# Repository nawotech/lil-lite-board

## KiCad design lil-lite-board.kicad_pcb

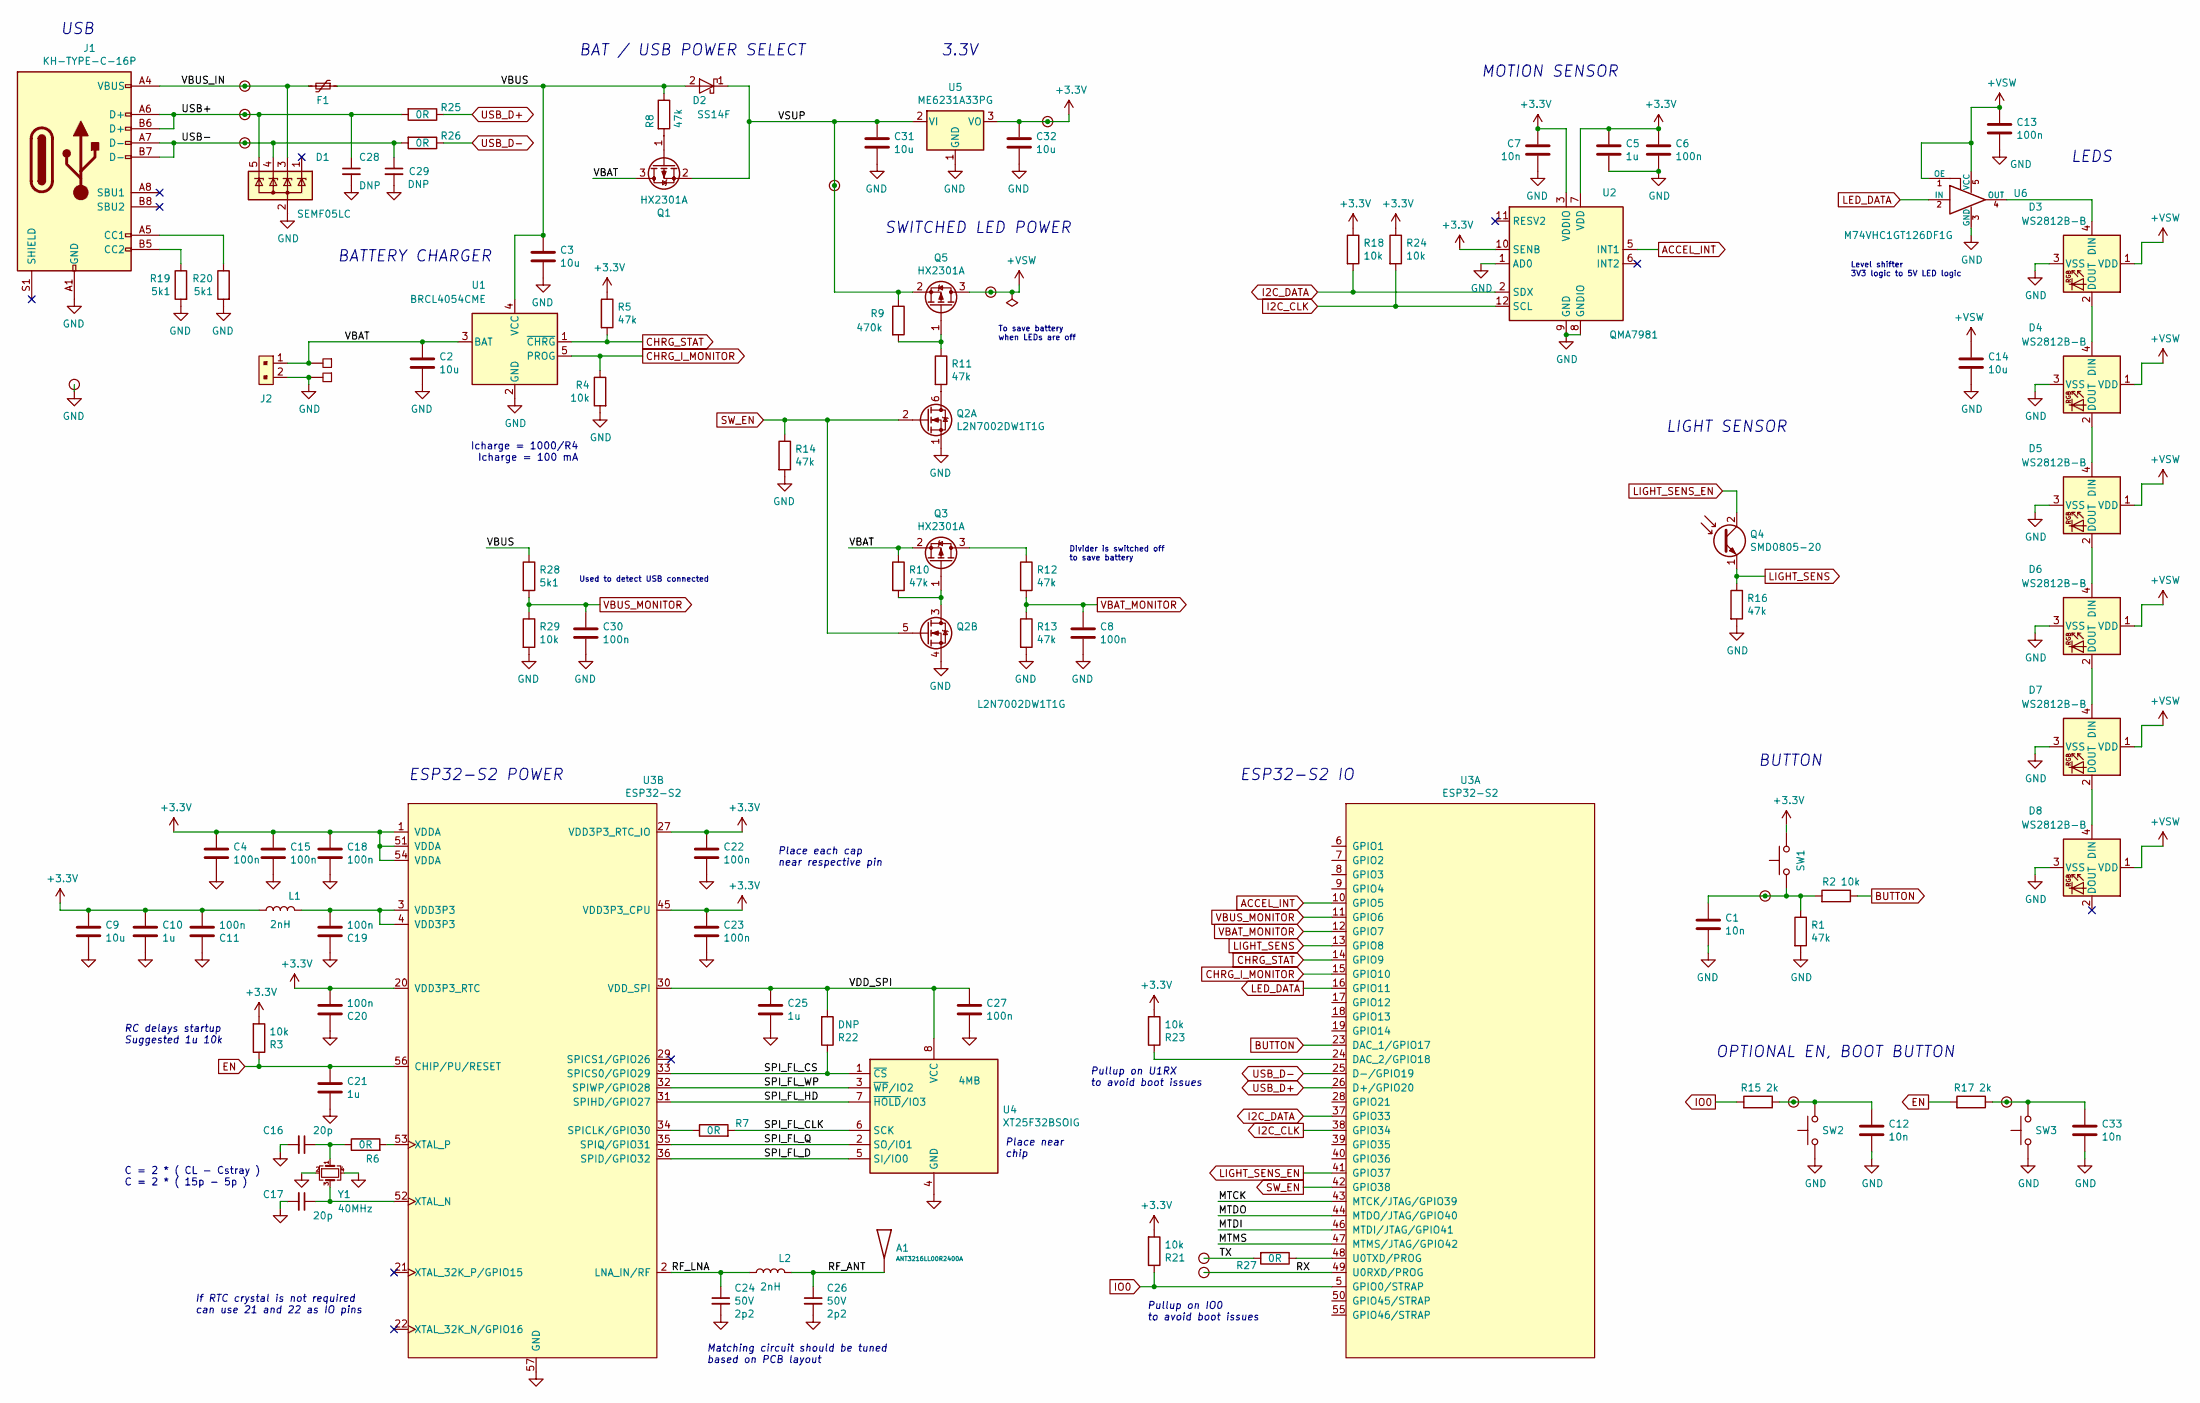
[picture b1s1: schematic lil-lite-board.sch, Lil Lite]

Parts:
A1: ANT3216LL00R2400A; Antenna_3216
C1, C7, C12, C33: 10n; C_0603_1608Metric; Voltage 100; LCSC Part Number C77439
C2, C3, C9, C14, C31, C32: 10u; C_0603_1608Metric; LCSC Part Number C319196
C4, C6, C8, C11, C13, C15, C18, C19, C20, C22, C23, C27, C30: 100n; C_0402_1005Metric; LCSC Part Number C60474
C5, C10, C21, C25: 1u; C_0402_1005Metric; LCSC Part Number C497333
C16, C17: C_0402_50V_COG_20p; C_0402_1005Metric; Voltage 50V
C24, C26: C_0402_50V_COG_2p2; C_0402_1005Metric; Voltage 50V
C28, C29: DNP; C_0402_1005Metric; Voltage 50V
D1: SEMF05LC; SOT-353_SC-70-5; LCSC Part Number C355236
D2: SS14F; D_SMA; LCSC Part Number C108832
D3, D4, D5, D6, D7, D8: WS2812B-B; LED_WS2812B_PLCC4_5.0x5.0mm_P3.2mm; LCSC Part Number C114586
F1: MF-FSMF050X-2; Fuse_0603_1608Metric; LCSC Part Number C210357
J1: KH-TYPE-C-16P; USB_C_Receptacle_KH-TYPE-C-16P
J2: S2B-PH-SM4-TB; PinHeader_2x1mm_P2mm_SMD_RA; MPN S2B-PH-SM4-TB(LF)(SN); Digi-Key_PN 455-1749-1-ND
L1, L2: HQ1005C2N0ST; L_0402_1005Metric
P2, P3: WirePad; Solder_Wire_Pad_5mmx3mm
Q1, Q3, Q5: HX2301A; SOT-23
Q2: L2N7002DW1T1G; SOT-363_SC-70-6
Q4: SMD0805-20; LED_0805_2012Metric; LCSC Part Number C250858
R1, R5, R8, R10, R11, R12, R13, R16: 47k; R_0402_1005Metric; LCSC Part Number C380741
R2, R3, R4, R18, R21, R23, R24: 10k; R_0402_1005Metric; LCSC Part Number C60490
R6, R7, R25, R26, R27: 0R; R_0402_1005Metric
R9: 470k; R_0402_1005Metric; LCSC Part Number C409715
R14: 47k; R_0402_1005Metric; Tolerance 1%
R15, R17: 2k; R_0402_1005Metric; LCSC Part Number C60490
R19, R20, R28: 5k1; R_0402_1005Metric
R22: DNP; R_0402_1005Metric
R29: 10k; R_0402_1005Metric
SW1: TS5220A; SW_SPST_TL3342
SW2, SW3: DNP; STO-060A16AB
TP5, TP6, TP7, TP8, TP9, TP10, TP11, TP12, TP14, TP17, TP18, TP19: TestPoint_ICT_1mm; ICT_TestPoint_Pad_D1.00mm
U1: BRCL4054CME; SOT-23-5; LCSC Part Number C305436
U2: QMA7981; LGA-12_2x2mm_P0.5mm
U3: ESP32-S2
U4: XT25F32BSOIG; SOIC-8_3.9x4.9mm_P1.27mm
U5: ME6231A33PG; SOT-89-3
U6: M74VHC1GT126DF1G; SOT-353_SC-70-5
Y1: X322540MPB4SI; Crystal_SMD_3225-4Pin_3.2x2.5mm

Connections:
+3V3: C4.1, C5.1, C6.1, C7.1, C9.1, C10.1, C11.2, C15.1, C18.1, C20.2, C22.1, C23.1, C32.1, L1.1, R3.2, R5.1, R18.1, R21.2, R23.2, R24.1, SW1.1, TP19.1, U2.3 (VDDIO), U2.7 (VDD), U2.10 (SENB), U3.1 (VDDA), U3.20 (VDD3P3_RTC), U3.27 (VDD3P3_RTC_IO), U3.45 (VDD3P3_CPU), U3.51 (VDDA), U3.54 (VDDA), U5.3 (VO)
+VSW: C13.1, C14.1, D3.1 (VDD), D4.1 (VDD), D5.1 (VDD), D6.1 (VDD), D7.1 (VDD), D8.1 (VDD), Q5.3 (D), TP18.1, U6.1 (OE), U6.5 (VCC)
/MTCK: U3.43 (MTCK/JTAG/GPIO39)
/MTDI: U3.46 (MTDI/JTAG/GPIO41)
/MTDO: U3.44 (MTDO/JTAG/GPIO40)
/MTMS: U3.47 (MTMS/JTAG/GPIO42)
/RF_ANT: A1.1, C26.1, L2.2
/RF_LNA: C24.1, L2.1, U3.2 (LNA_IN/RF)
/RX: TP11.1, U3.49 (U0RXD/PROG)
/SPI_FL_CLK: R7.2, U4.6 (SCK)
/SPI_FL_CS: R22.1, U3.33 (SPICS0/GPIO29), U4.1 (~CS)
/SPI_FL_D: U3.36 (SPID/GPIO32), U4.5 (SI/IO0)
/SPI_FL_HD: U3.31 (SPIHD/GPIO27), U4.7 (~HOLD~/IO3)
/SPI_FL_Q: U3.35 (SPIQ/GPIO31), U4.2 (SO/IO1)
/SPI_FL_WP: U3.32 (SPIWP/GPIO28), U4.3 (~WP~/IO2)
/TX: R27.2, TP10.1
/USB+: C28.1, D1.5 (K), J1.A6 (D+), J1.B6 (D+), R25.2, TP6.1
/USB-: C29.1, D1.4 (K), J1.A7 (D-), J1.B7 (D-), R26.2, TP7.1
/VBAT: C2.1, J2.1, P2.1, Q1.3 (D), Q3.2 (S), R10.1, U1.3 (BAT)
/VBUS: C3.1, D2.2 (A), F1.1, R8.1, R28.1, U1.4 (VCC)
/VBUS_IN: D1.3 (K), F1.2, J1.A4 (VBUS), J1.A9 (VBUS), J1.B4 (VBUS), J1.B9 (VBUS), TP9.1
/VDD_SPI: C25.1, C27.1, R22.2, U3.30 (VDD_SPI), U4.8 (VCC)
/VSUP: C31.1, D2.1 (K), Q1.2 (S), Q5.2 (S), R9.1, TP17.1, U5.2 (VI)
ACCEL_INT: U2.5 (INT1), U3.10 (GPIO5)
BUTTON: R2.1, U3.23 (DAC_1/GPIO17)
CHRG_I_MONITOR: R4.1, U1.5 (PROG), U3.15 (GPIO10)
CHRG_STAT: R5.2, U1.1 (~CHRG), U3.14 (GPIO9)
EN: C21.1, R3.1, R17.2, U3.56 (CHIP/PU/RESET)
GND: C1.2, C2.2, C3.2, C4.2, C5.2, C6.2, C7.2, C8.2, C9.2, C10.2, C11.1, C12.2, C13.2, C14.2, C15.2, C16.2, C17.2, C18.2, C19.1, C20.1, C21.2, C22.2, C23.2, C24.2, C25.2, C26.2, C27.2, C28.2, C29.2, C30.2, C31.2, C32.2, C33.2, D1.2 (A), D3.3 (VSS), D4.3 (VSS), D5.3 (VSS), D6.3 (VSS), D7.3 (VSS), D8.3 (VSS), J1.A1 (GND), J1.A12 (GND), J1.B1 (GND), J1.B12 (GND), J2.2, P3.1, Q2.1 (S), Q2.4 (S), R1.2, R4.2, R13.2, R14.2, R16.2, R19.2, R20.2, R29.2, SW2.1, SW3.1, TP5.1, U1.2 (GND), U2.1 (AD0), U2.8 (GNDIO), U2.9 (GND), U3.57 (GND), U4.4 (GND), U5.1 (GND), U6.3 (GND), Y1.2, Y1.4
I2C_CLK: R24.2, U2.12 (SCL), U3.38 (GPIO34)
I2C_DATA: R18.2, U2.2 (SDX), U3.37 (GPIO33)
IO0: R15.2, R21.1, U3.5 (GPIO0/STRAP)
LED_DATA: U3.16 (GPIO11), U6.2 (IN)
LIGHT_SENS: Q4.1 (E), R16.1, U3.13 (GPIO8)
LIGHT_SENS_EN: Q4.2 (C), U3.41 (GPIO37)
unnamed: C1.1, R1.1, R2.2, SW1.2, TP8.1
unnamed: C12.1, R15.1, SW2.2, TP14.1
unnamed: C16.1, R6.1, Y1.1
unnamed: C17.1, U3.52 (XTAL_N), Y1.3
unnamed: C19.2, L1.2, U3.3 (VDD3P3), U3.4 (VDD3P3)
unnamed: C33.1, R17.1, SW3.2, TP12.1
unnamed: D3.2 (DOUT), D4.4 (DIN)
unnamed: D3.4 (DIN), U6.4 (OUT)
unnamed: D4.2 (DOUT), D5.4 (DIN)
unnamed: D5.2 (DOUT), D6.4 (DIN)
unnamed: D6.2 (DOUT), D7.4 (DIN)
unnamed: D7.2 (DOUT), D8.4 (DIN)
unnamed: J1.A5 (CC1), R20.1
unnamed: J1.B5 (CC2), R19.1
unnamed: Q1.1 (G), R8.2
unnamed: Q2.3 (D), Q3.1 (G), R10.2
unnamed: Q2.6 (D), R11.2
unnamed: Q3.3 (D), R12.1
unnamed: Q5.1 (G), R9.2, R11.1
unnamed: R6.2, U3.53 (XTAL_P)
unnamed: R7.1, U3.34 (SPICLK/GPIO30)
unnamed: R23.1, U3.24 (DAC_2/GPIO18)
unnamed: R27.1, U3.48 (U0TXD/PROG)
SW_EN: Q2.2 (G), Q2.5 (G), R14.1, U3.42 (GPIO38)
USB_D+: R25.1, U3.26 (D+/GPIO20)
USB_D-: R26.1, U3.25 (D-/GPIO19)
VBAT_MONITOR: C8.1, R12.2, R13.1, U3.12 (GPIO7)
VBUS_MONITOR: C30.1, R28.2, R29.1, U3.11 (GPIO6)

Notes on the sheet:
RC delays startup Suggested 1u 10k
C = 2 * ( CL - Cstray ) C = 2 * ( 15p - 5p )
If RTC crystal is not required can use 21 and 22 as IO pins
Pullup on U1RX to avoid boot issues
Place near chip
LEDS
Matching circuit should be tuned based on PCB layout
Icharge = 1000/R4 Icharge = 100 mA
MOTION SENSOR
LIGHT SENSOR
BUTTON
Level shifter 3V3 logic to 5V LED logic
3.3V
SWITCHED LED POWER
To save battery when LEDs are off
Divider is switched off to save battery
Used to detect USB connected
BATTERY CHARGER
USB
ESP32-S2 POWER
ESP32-S2 IO
BAT / USB POWER SELECT
Place each cap near respective pin
OPTIONAL EN, BOOT BUTTON
Pullup on IO0 to avoid boot issues

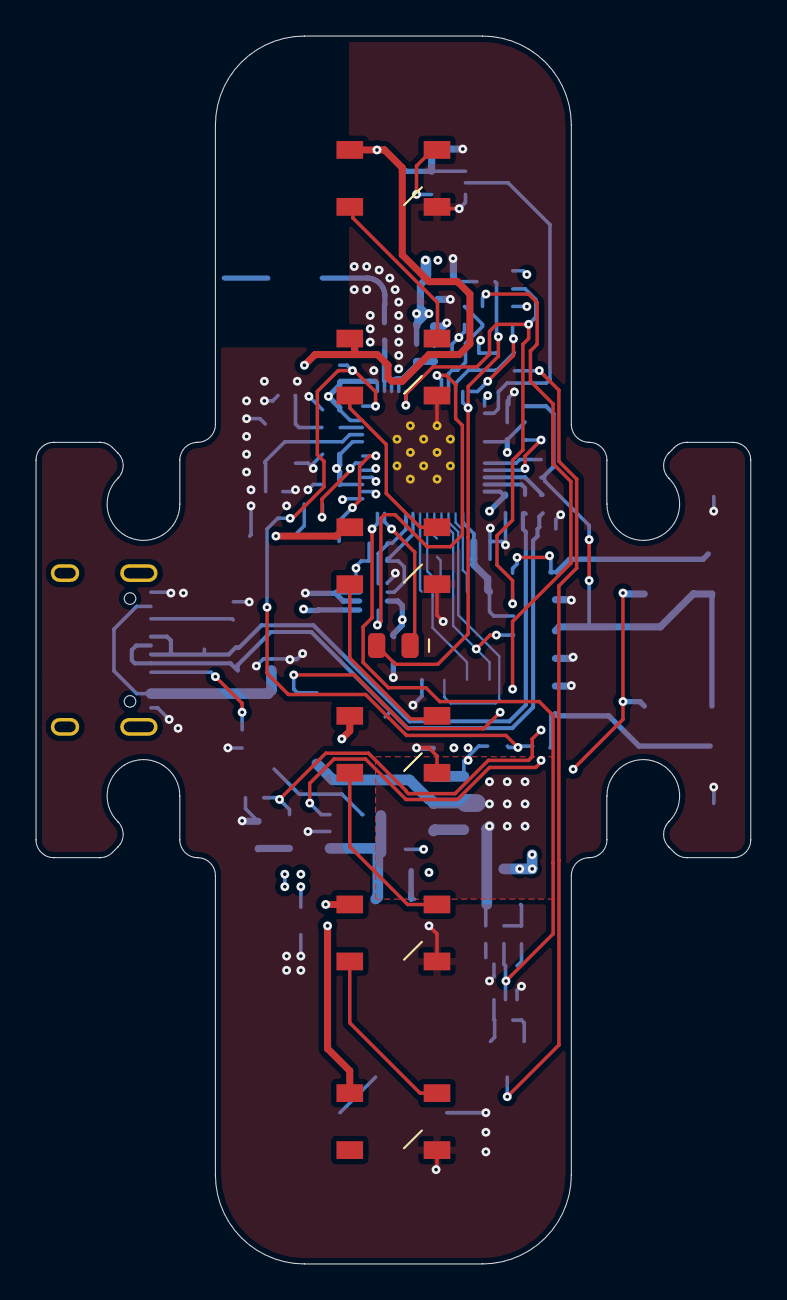
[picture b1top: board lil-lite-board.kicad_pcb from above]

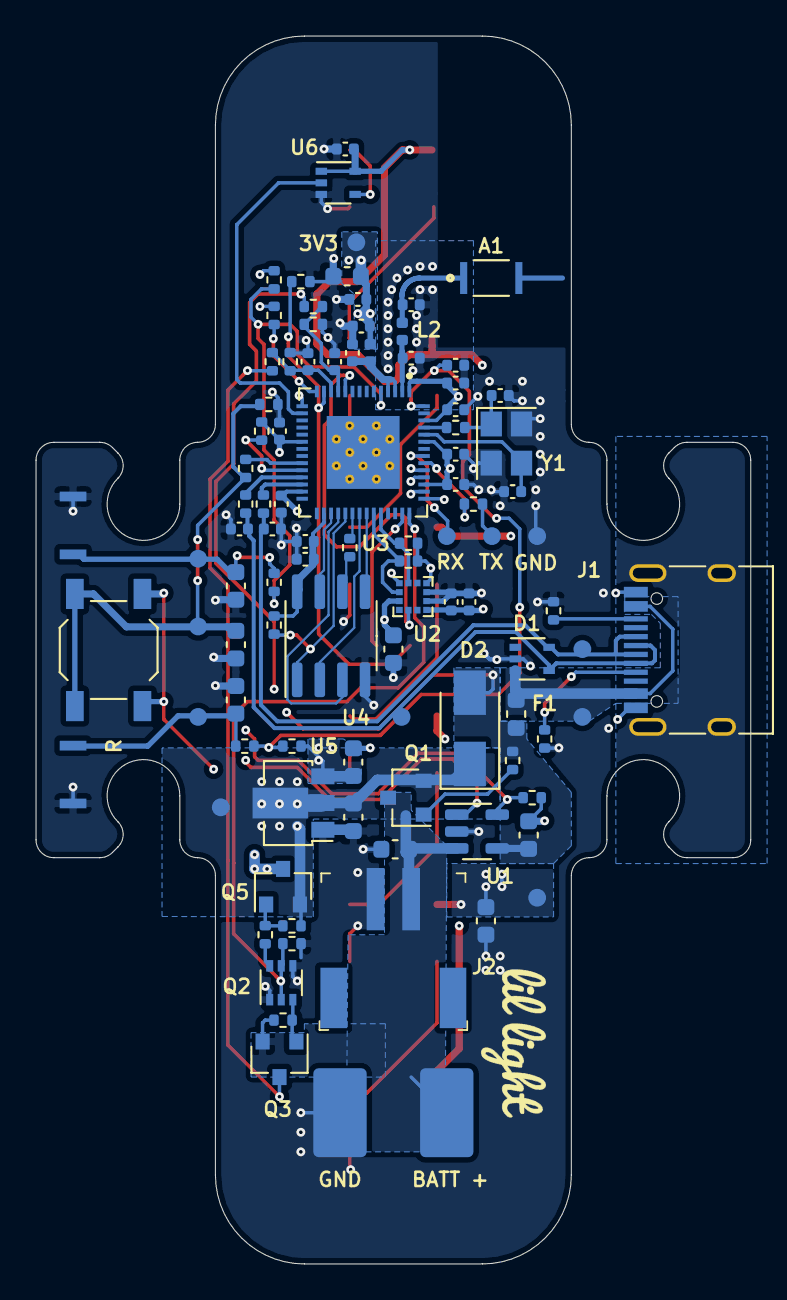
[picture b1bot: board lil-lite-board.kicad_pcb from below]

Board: 4 copper layers, 40.2 x 69.0 mm, 106 parts (99 on the bottom side), 59 nets.

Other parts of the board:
LG3: LOGO; Logo_Lil_Light_Long

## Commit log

2020-04-05 update gitignore
2020-04-05 update logo and BOM
2020-04-15 add schematic pdf
2020-05-06 update assemby drawing layer
2020-05-06 remove front led caps
2020-05-06 update 3d models
2020-05-06 remove old v1 files
2021-01-09 update broken library
2021-07-20 update board
2021-07-26 update to esp32-s2
2021-07-29 more updates
2021-08-01 clean up schematic
2021-08-05 placement
2021-08-07 routing done
2021-08-07 fix slkscreen
2021-08-07 Update BOM
2021-08-08 update schematic title block
2021-08-29 update flash chip to 4MB and divider for VBUS
2021-09-29 update flash chip to faster version
2021-10-05 add sw pn
2021-10-06 remove fab files
2021-10-14 update JCLPCB part numbers
2021-10-14 add 10k to IO0 pin to fix boot issue
2021-10-18 update file names
2021-10-18 update file generation commands
2021-10-25 Change VBUS divider for digital in
2021-10-29 remove via in pad from dfm
